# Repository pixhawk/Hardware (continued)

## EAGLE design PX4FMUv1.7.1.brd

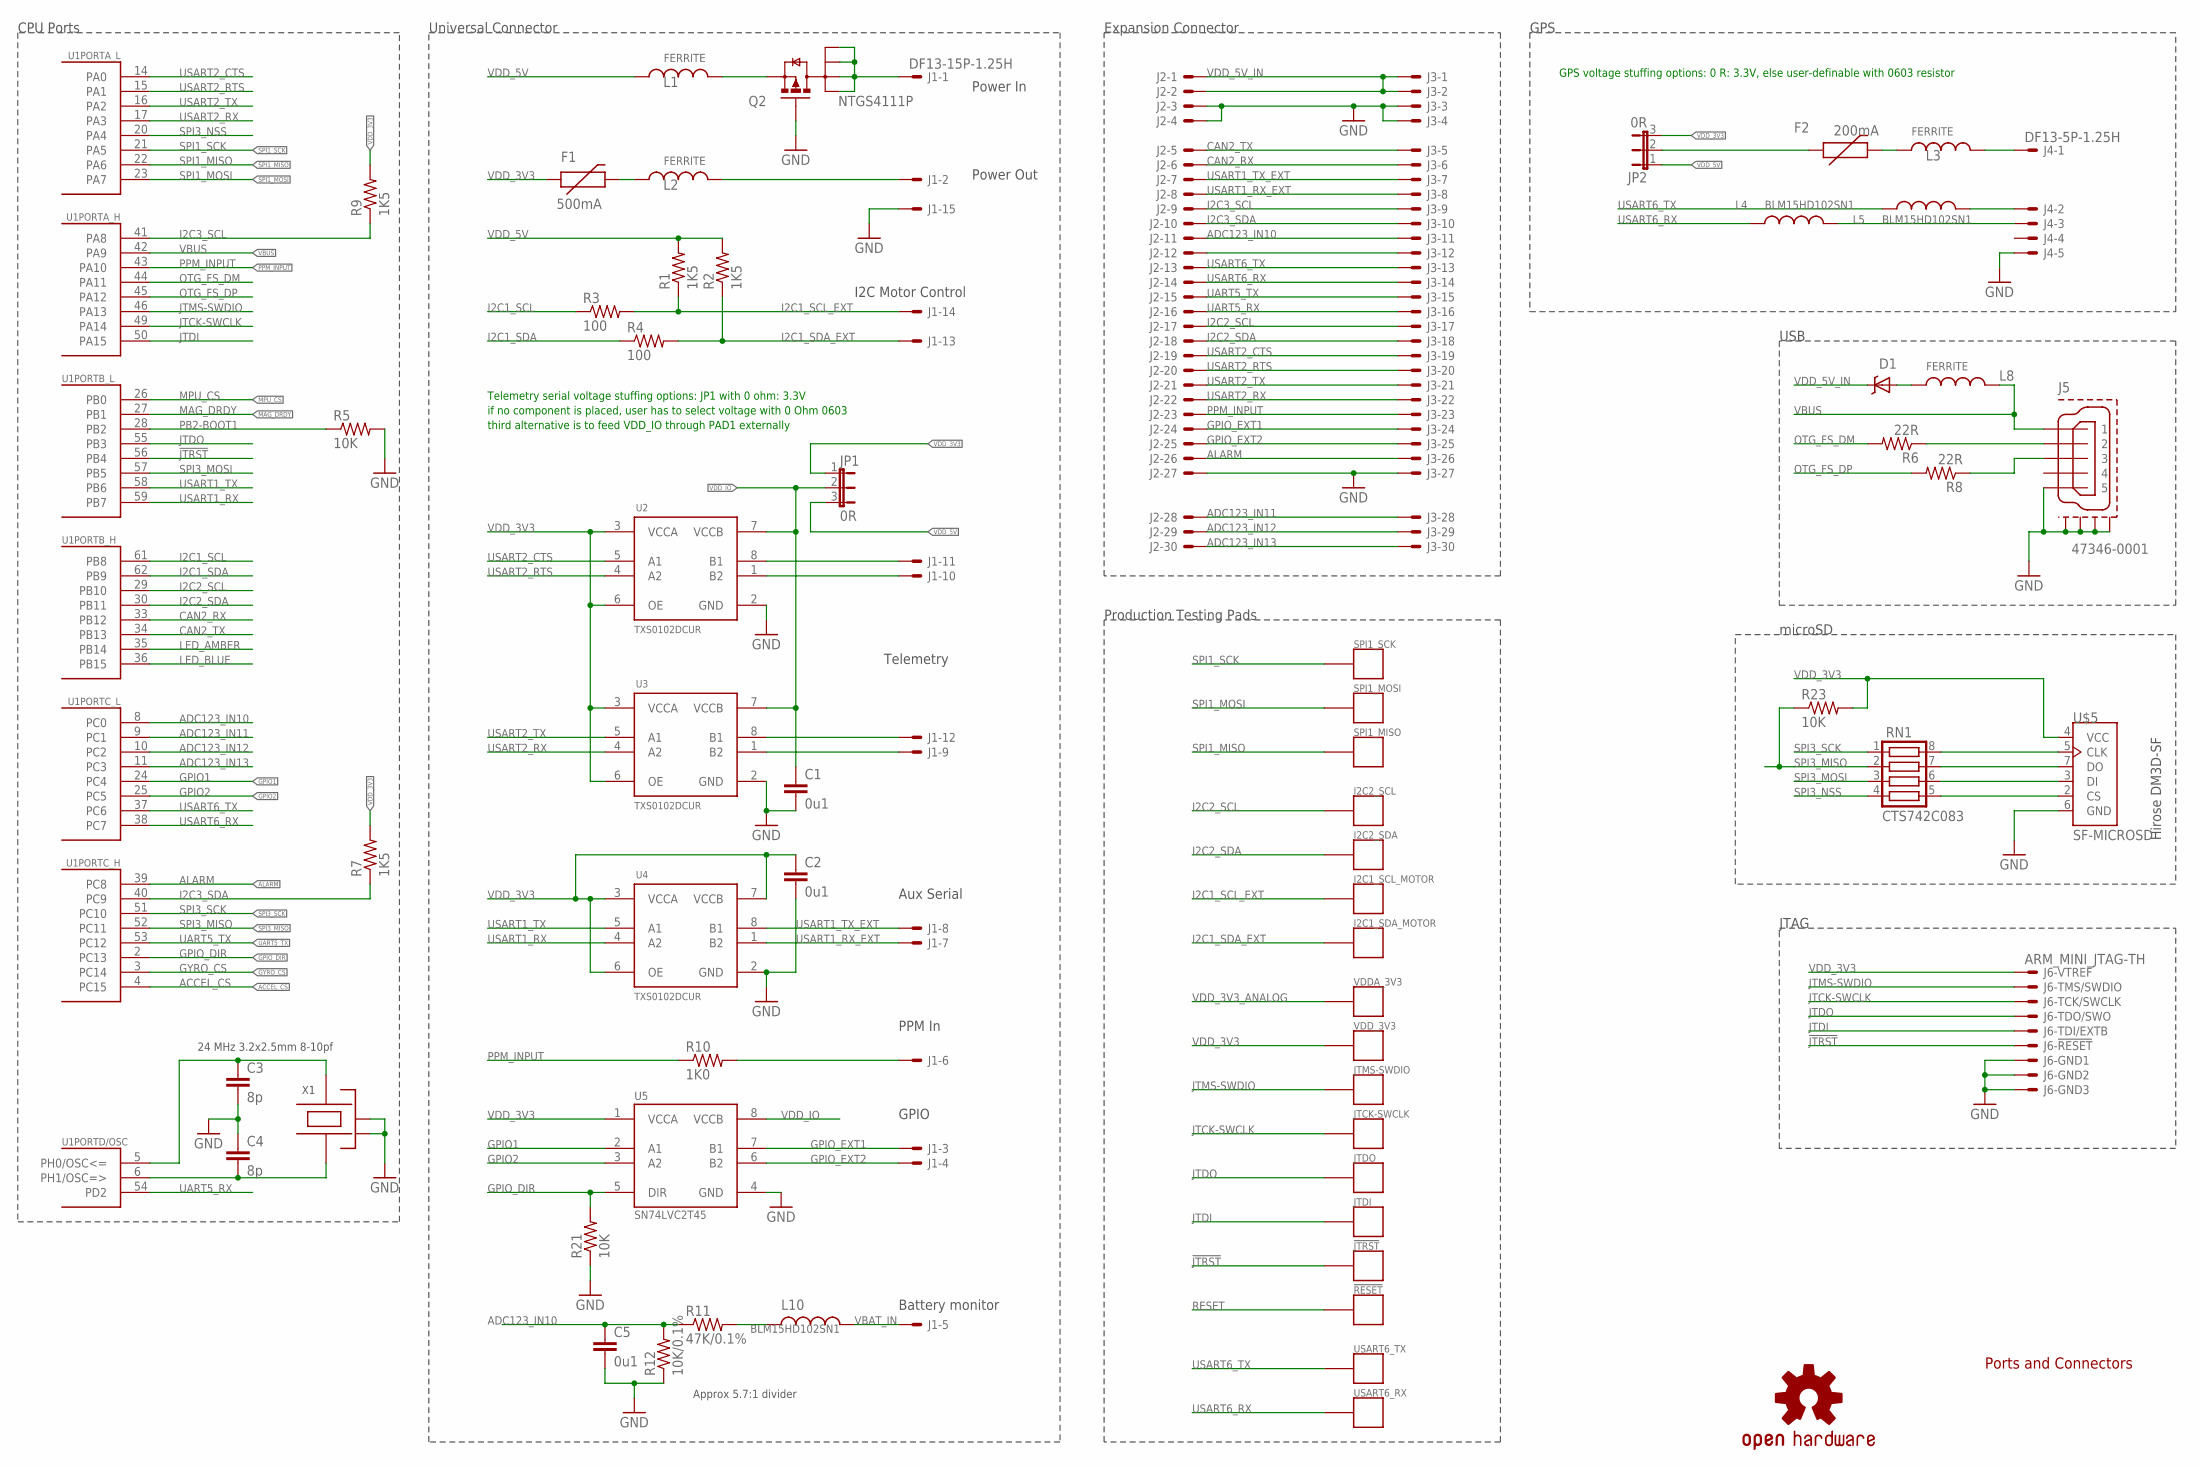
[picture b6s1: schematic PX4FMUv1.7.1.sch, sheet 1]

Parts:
!JTRST: PAD.04; PAD.04X.04; PARTNO *
!RESET: PAD.04; PAD.04X.04; PARTNO *
C1, C2, C5: 0u1; 0402-CAP; PARTNO CC0402ZRY5V7BB104
C3, C4: 8p; 0402-CAP; PARTNO C1005C0G1H080C
D1: MSS1P4-M3; MICROSMP; PARTNO MSS1P4-M3/89A
F1: 500mA; 0402-PTC; PARTNO MF-FSMF050X-2
F2: 200mA; 0402-PTC; PARTNO MF-FSMF020X-2
I2C1_SCL_MOTOR, I2C1_SDA_MOTOR, I2C2_SCL: PAD.03; PAD.03X.03; PARTNO *
I2C2_SDA: PAD.04; PAD.04X.04; PARTNO *
J1: DF13-15P-1.25H; DF13A-15P-1.25H; PARTNO DF13A-15P-1.25H(20)
J2: HEADER_2X15-REV; HEADER_2MM_2X15_REVERSE; PARTNO 953230-2000-AR-PR
J3: HEADER_2X15; HEADER_2MM_2X15; PARTNO 953230-2000-AR-PR
J4: DF13-5P-1.25H; DF13A-5P-1.25H; PARTNO DF13A-5P-1.25H(20)
J5: 47346-0001; MOLEX-47346-0001; PARTNO 47346-0001
J6: ARM_MINI_JTAG-TH; FTSH-105-01-XXX-DV; PARTNO M50-3900542
JP1, JP2: 0R; SJ_3_0603_PASTE1&2; PARTNO RMCF0402ZT0R00
JTCK-SWCLK: PAD.04; PAD.04X.04; PARTNO *
JTDI: PAD.04; PAD.04X.04; PARTNO *
JTDO: PAD.04; PAD.04X.04; PARTNO *
JTMS-SWDIO: PAD.04; PAD.04X.04; PARTNO *
L1, L2, L3, L8: FERRITE; 0402-IND; PARTNO BKP1005HS121-T
L4, L5, L10: BLM15HD102SN1; 0402-IND; PARTNO BLM15HD102SN1
Q2: NTGS4111P; TSOP-6; PARTNO NTGS4111P
R1, R2, R7, R9: 1K5; 0402-RES; PARTNO RMCF0402JT1K50
R3, R4: 100; 0402-RES; PARTNO RMCF0402JT100R
R5, R21, R23: 10K; 0402-RES; PARTNO RMCF0402FT10K0
R6, R8: 22R; 0402-RES; PARTNO RMCF0402JT22R0
R10: 1K0; 0402-RES; PARTNO RMCF0402JT1K00
R11: 47K/0.1%; 0402-RES; PARTNO ERA-2AEB473X
R12: 10K/0.1%; 0402-RES; PARTNO ERA-2AEB103X
RN1: CTS742C083; PARTNO TC164-JR-07100RL
SPI1_MISO, SPI1_MOSI, SPI1_SCK: PAD.04; PAD.04X.04; PARTNO *
U1: STM32F405RGT6; TQFP64; PARTNO STM32F405RGT6
U2, U3, U4: TXS0102DCUR; TI-DCU; PARTNO TXS0102DCUR
U5: SN74LVC2T45; TI-DCU; PARTNO SN74LVC2T45
U$5: SF-MICROSD; MICROSD
U$7: OSHW-LOGOS; OSHW-LOGO-S; PARTNO *
USART6_RX, USART6_TX: PAD.04; PAD.04X.04; PARTNO *
VDDA_3V3: PAD.04; PAD.04X.04; PARTNO *
VDD_3V3: PAD.04; PAD.04X.04; PARTNO *
X1: 24 MHz 3.2x2.5mm 8-10pf; OSCILLATOR-3.2X2.5; PARTNO NX3225SA-24.000000MHZ

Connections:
!JTRST: !JTRST.P$1, J6.10, U1.56 (PB4)
ACCEL_CS: U1.4 (PC15)
ADC123_IN10: C5.1, J2.11, J3.11, R11.1, R12.2, U1.8 (PC0)
ADC123_IN11: J2.28, J3.28, U1.9 (PC1)
ADC123_IN12: J2.29, J3.29, U1.10 (PC2)
ADC123_IN13: J2.30, J3.30, U1.11 (PC3); also elsewhere on the board
ALARM: J2.26, J3.26, U1.39 (PC8); also elsewhere on the board
CAN2_RX: J2.6, J3.6, U1.33 (PB12)
CAN2_TX: J2.5, J3.5, U1.34 (PB13)
GND: C1.2, C2.2, C3.2, C4.1, C5.2, J1.15, J2.3, J2.4, J2.27, J3.3, J3.4, J3.27, J4.5, J5.GND (5), J5.GND1, J5.GND2, J5.GND3, J5.GND4, J6.3, J6.5, J6.9, Q2.3 (G), R5.2, R12.1, R21.1, U2.2 (GND), U3.2 (GND), U4.2 (GND), U5.4 (GND), U$5.6 (GND), X1.2 (NC_2), X1.4 (NC_4); also elsewhere on the board
GPIO1: U1.24 (PC4), U5.2 (A1)
GPIO2: U1.25 (PC5), U5.3 (A2)
GPIO_DIR: R21.2, U1.2 (PC13), U5.5 (DIR)
GPIO_EXT1: J1.3, J2.24, J3.24, U5.7 (B1)
GPIO_EXT2: J1.4, J2.25, J3.25, U5.6 (B2)
GYRO_CS: U1.3 (PC14); also elsewhere on the board
I2C1_SCL: R3.1, U1.61 (PB8)
I2C1_SCL_EXT: I2C1_SCL_MOTOR.P$1, J1.14, R1.1, R3.2
I2C1_SDA: R4.1, U1.62 (PB9)
I2C1_SDA_EXT: I2C1_SDA_MOTOR.P$1, J1.13, R2.1, R4.2
I2C2_SCL: I2C2_SCL.P$1, J2.17, J3.17, U1.29 (PB10); also elsewhere on the board
I2C2_SDA: I2C2_SDA.P$1, J2.18, J3.18, U1.30 (PB11); also elsewhere on the board
I2C3_SCL: J2.9, J3.9, R9.1, U1.41 (PA8)
I2C3_SDA: J2.10, J3.10, R7.1, U1.40 (PC9)
JTCK-SWCLK: J6.4, JTCK-SWCLK.P$1, U1.49 (PA14)
JTDI: J6.8, JTDI.P$1, U1.50 (PA15)
JTDO: J6.6, JTDO.P$1, U1.55 (PB3)
JTMS-SWDIO: J6.2, JTMS-SWDIO.P$1, U1.46 (PA13)
LED_AMBER: U1.35 (PB14); also elsewhere on the board
LED_BLUE: U1.36 (PB15); also elsewhere on the board
MAG_DRDY: U1.27 (PB1); also elsewhere on the board
MPU_CS: U1.26 (PB0); also elsewhere on the board
unnamed: C4.2, U1.6 (PH1/OSC=>), X1.1
unnamed: C3.1, U1.5 (PH0/OSC<=), X1.3
unnamed: J1.2, L2.2
unnamed: F2.2, L3.1
unnamed: J4.2, L5.2
unnamed: J4.3, L4.2
unnamed: J1.11, U2.8 (B1)
unnamed: J1.10, U2.1 (B2)
unnamed: L1.2, Q2.4 (S)
unnamed: J1.12, U3.8 (B1)
unnamed: J1.9, U3.1 (B2)
unnamed: F2.1, JP2.2
unnamed: J2.12, J3.12
unnamed: RN1.5, U$5.2 (CS)
unnamed: D1.ANODE (A), L8.1
unnamed: J4.1, L3.2
unnamed: RN1.6, U$5.3 (DI)
unnamed: F1.2, L2.1
unnamed: RN1.7, U$5.7 (DO)
unnamed: RN1.8, U$5.5 (CLK)
unnamed: L10.1, R11.2
unnamed: J1.1, Q2.1 (D), Q2.2 (D1), Q2.5 (D2), Q2.6 (D3)
OTG_DM: J5.D- (2), R6.1
OTG_DP: J5.D+ (3), R8.1
OTG_FS_DM: R6.2, U1.44 (PA11)
OTG_FS_DP: R8.2, U1.45 (PA12)
PB2-BOOT1: R5.1, U1.28 (PB2)
PPM_INPUT: J2.23, J3.23, R10.1, U1.43 (PA10)
PPM_INPUT_CON: J1.6, R10.2
RESET: !RESET.P$1; also elsewhere on the board
SPI1_MISO: SPI1_MISO.P$1, U1.22 (PA6); also elsewhere on the board
SPI1_MOSI: SPI1_MOSI.P$1, U1.23 (PA7); also elsewhere on the board
SPI1_SCK: SPI1_SCK.P$1, U1.21 (PA5); also elsewhere on the board
SPI3_MISO: R23.1, RN1.2, U1.52 (PC11)
SPI3_MOSI: RN1.3, U1.57 (PB5)
SPI3_NSS: RN1.4, U1.20 (PA4)
SPI3_SCK: RN1.1, U1.51 (PC10)
UART5_RX: J2.16, J3.16, U1.54 (PD2)
UART5_TX: J2.15, J3.15, U1.53 (PC12)
USART1_RX: U1.59 (PB7), U4.4 (A2)
USART1_RX_EXT: J1.7, J2.8, J3.8, U4.1 (B2)
USART1_TX: U1.58 (PB6), U4.5 (A1)
USART1_TX_EXT: J1.8, J2.7, J3.7, U4.8 (B1)
USART2_CTS: J2.19, J3.19, U1.14 (PA0), U2.5 (A1)
USART2_RTS: J2.20, J3.20, U1.15 (PA1), U2.4 (A2)
USART2_RX: J2.22, J3.22, U1.17 (PA3), U3.4 (A2)
USART2_TX: J2.21, J3.21, U1.16 (PA2), U3.5 (A1)
USART6_RX: J2.14, J3.14, L4.1, U1.38 (PC7), USART6_RX.P$1
USART6_TX: J2.13, J3.13, L5.1, U1.37 (PC6), USART6_TX.P$1
VBAT_IN: J1.5, L10.2; also elsewhere on the board
VBUS: J5.VBUS (1), L8.2, U1.42 (PA9)
VDD_3V3: C2.1, F1.1, J6.1, JP1.1, JP2.3, R7.2, R9.2, R23.2, U2.3 (VCCA), U2.6 (OE), U3.3 (VCCA), U3.6 (OE), U4.3 (VCCA), U4.6 (OE), U4.7 (VCCB), U5.1 (VCCA), U$5.4 (VCC), VDD_3V3.P$1; also elsewhere on the board
VDD_3V3_ANALOG: VDDA_3V3.P$1; also elsewhere on the board
VDD_5V: JP1.3, JP2.1, L1.1, R1.2, R2.2; also elsewhere on the board
VDD_5V_IN: D1.CATHODE (C), J2.1, J2.2, J3.1, J3.2; also elsewhere on the board
VDD_IO: C1.1, JP1.2, U2.7 (VCCB), U3.7 (VCCB), U5.8 (VCCB)

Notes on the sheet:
Ports and Connectors
Telemetry
I2C Motor Control
Power In
Battery monitor
GPIO
Approx 5.7:1 divider
CPU Ports
Universal Connector
GPS
USB
JTAG
GPS voltage stuffing options: 0 R: 3.3V, else user-definable with 0603 resistor
Telemetry serial voltage stuffing options: JP1 with 0 ohm: 3.3V
Aux Serial
PPM In
Expansion Connector
if no component is placed, user has to select voltage with 0 Ohm 0603
Production Testing Pads
Power Out
microSD
third alternative is to feed VDD_IO through PAD1 externally
Hirose DM3D-SF

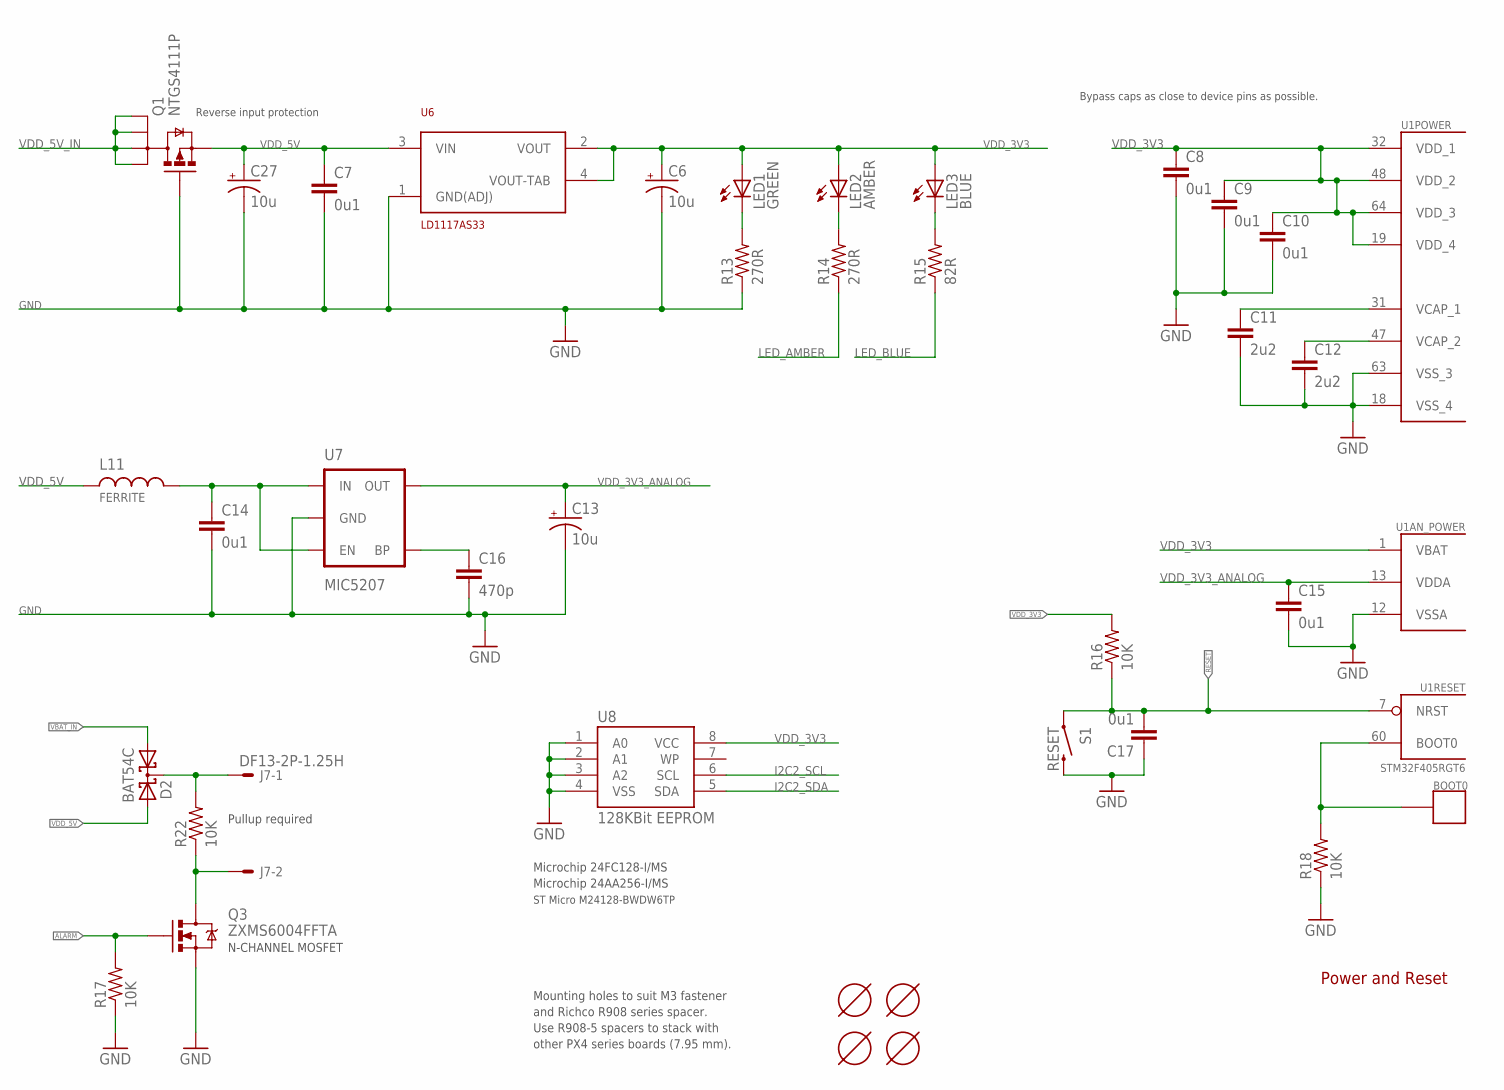
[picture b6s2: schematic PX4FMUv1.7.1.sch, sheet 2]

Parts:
BOOT0: PAD.04; PAD.04X.04; PARTNO *
C6, C13, C27: 10u; EIA3216; PARTNO F931A106MAA
C7, C8, C9, C10, C14, C15, C17: 0u1; 0402-CAP; PARTNO CC0402ZRY5V7BB104
C11, C12: 2u2; 0402-CAP; PARTNO C1608Y5V1C225Z
C16: 470p; 0402-CAP; PARTNO CC0402KRX7R9BB471
D2: BAT54C; SOT23-3; PARTNO BAT54C-7-F
J7: DF13-2P-1.25H; DF13A-2P-1.25H; PARTNO DF13-2P-1.25H(20)
L11: FERRITE; 0402-IND; PARTNO BKP1005HS121-T
LED1: GREEN; LED-0603; PARTNO LNJ337W83RA
LED2: AMBER; LED-0603; PARTNO LNJ437W84RA
LED3: BLUE; LED-0603; PARTNO LNJ937W8CRA
Q1: NTGS4111P; TSOP-6; PARTNO NTGS4111P
Q3: ZXMS6004FFTA; SOT23-3; PARTNO ZXMS6004FFTA
R13, R14: 270R; 0402-RES; PARTNO RC0402JR-07270RL
R15: 82R; 0402-RES; PARTNO RC0402JR-0782RL
R16, R17, R18, R22: 10K; 0402-RES; PARTNO RMCF0402FT10K0
S1: RESET; EVQP7J01K; PARTNO EVQP7J01K
U1: STM32F405RGT6; TQFP64; PARTNO STM32F405RGT6
U6: LD1117AS33; SOT-223; PARTNO LD1117AS33
U7: MIC5207; SOT23-5; PARTNO MIC5207-3.3YM5
U8: 128KBit EEPROM; MSOP-8; PARTNO 24FC128-I/MS
U$1, U$2, U$3, U$4: MOUNT-HOLE3.1MM; MOUNT-HOLE3.1; PARTNO *

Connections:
ALARM: Q3.1 (G), R17.2; also elsewhere on the board
BOOT0: BOOT0.P$1, R18.2, U1.60 (BOOT0)
GND: C6.C (-), C7.2, C8.2, C9.2, C10.2, C11.2, C12.2, C13.C (-), C14.2, C15.2, C16.2, C17.1, C27.C (-), Q1.3 (G), Q3.2 (S), R13.1, R17.1, R18.1, S1.B3 (2), U1.12 (VSSA), U1.18 (VSS_4), U1.63 (VSS_3), U6.1 (GND(ADJ)), U7.2 (GND), U8.1 (A0), U8.2 (A1), U8.3 (A2), U8.4 (VSS); also elsewhere on the board
I2C2_SCL: U8.6 (SCL); also elsewhere on the board
I2C2_SDA: U8.5 (SDA); also elsewhere on the board
LED_AMBER: R14.1; also elsewhere on the board
LED_BLUE: R15.1; also elsewhere on the board
unnamed: D2.3 (CC), J7.1, R22.2
unnamed: C16.1, U7.4 (BP)
unnamed: J7.2, Q3.3 (D), R22.1
unnamed: LED3.C, R15.2
unnamed: LED1.C, R13.2
unnamed: LED2.C, R14.2
unnamed: C14.1, L11.2, U7.1 (IN), U7.3 (EN)
RESET: C17.2, R16.1, S1.A1 (1), U1.7 (NRST); also elsewhere on the board
VBAT_IN: D2.1 (A1); also elsewhere on the board
VCAP_1: C11.1, U1.31 (VCAP_1)
VCAP_2: C12.1, U1.47 (VCAP_2)
VDD_3V3: C6.A (+), C8.1, C9.1, C10.1, LED1.A, LED2.A, LED3.A, R16.2, U1.1 (VBAT), U1.19 (VDD_4), U1.32 (VDD_1), U1.48 (VDD_2), U1.64 (VDD_3), U6.2 (VOUT), U6.4 (VOUT-TAB), U8.8 (VCC); also elsewhere on the board
VDD_3V3_ANALOG: C13.A (+), C15.1, U1.13 (VDDA), U7.5 (OUT); also elsewhere on the board
VDD_5V: C7.1, C27.A (+), D2.2 (A2), L11.1, Q1.4 (S), U6.3 (VIN); also elsewhere on the board
VDD_5V_IN: Q1.1 (D), Q1.2 (D1), Q1.5 (D2), Q1.6 (D3); also elsewhere on the board

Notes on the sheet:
Power and Reset
Bypass caps as close to device pins as possible.
Microchip 24FC128-I/MS
Microchip 24AA256-I/MS
Mounting holes to suit M3 fastener
and Richco R908 series spacer.
ST Micro M24128-BWDW6TP
Reverse input protection
N-CHANNEL MOSFET
Pullup required
Use R908-5 spacers to stack with
other PX4 series boards (7.95 mm).

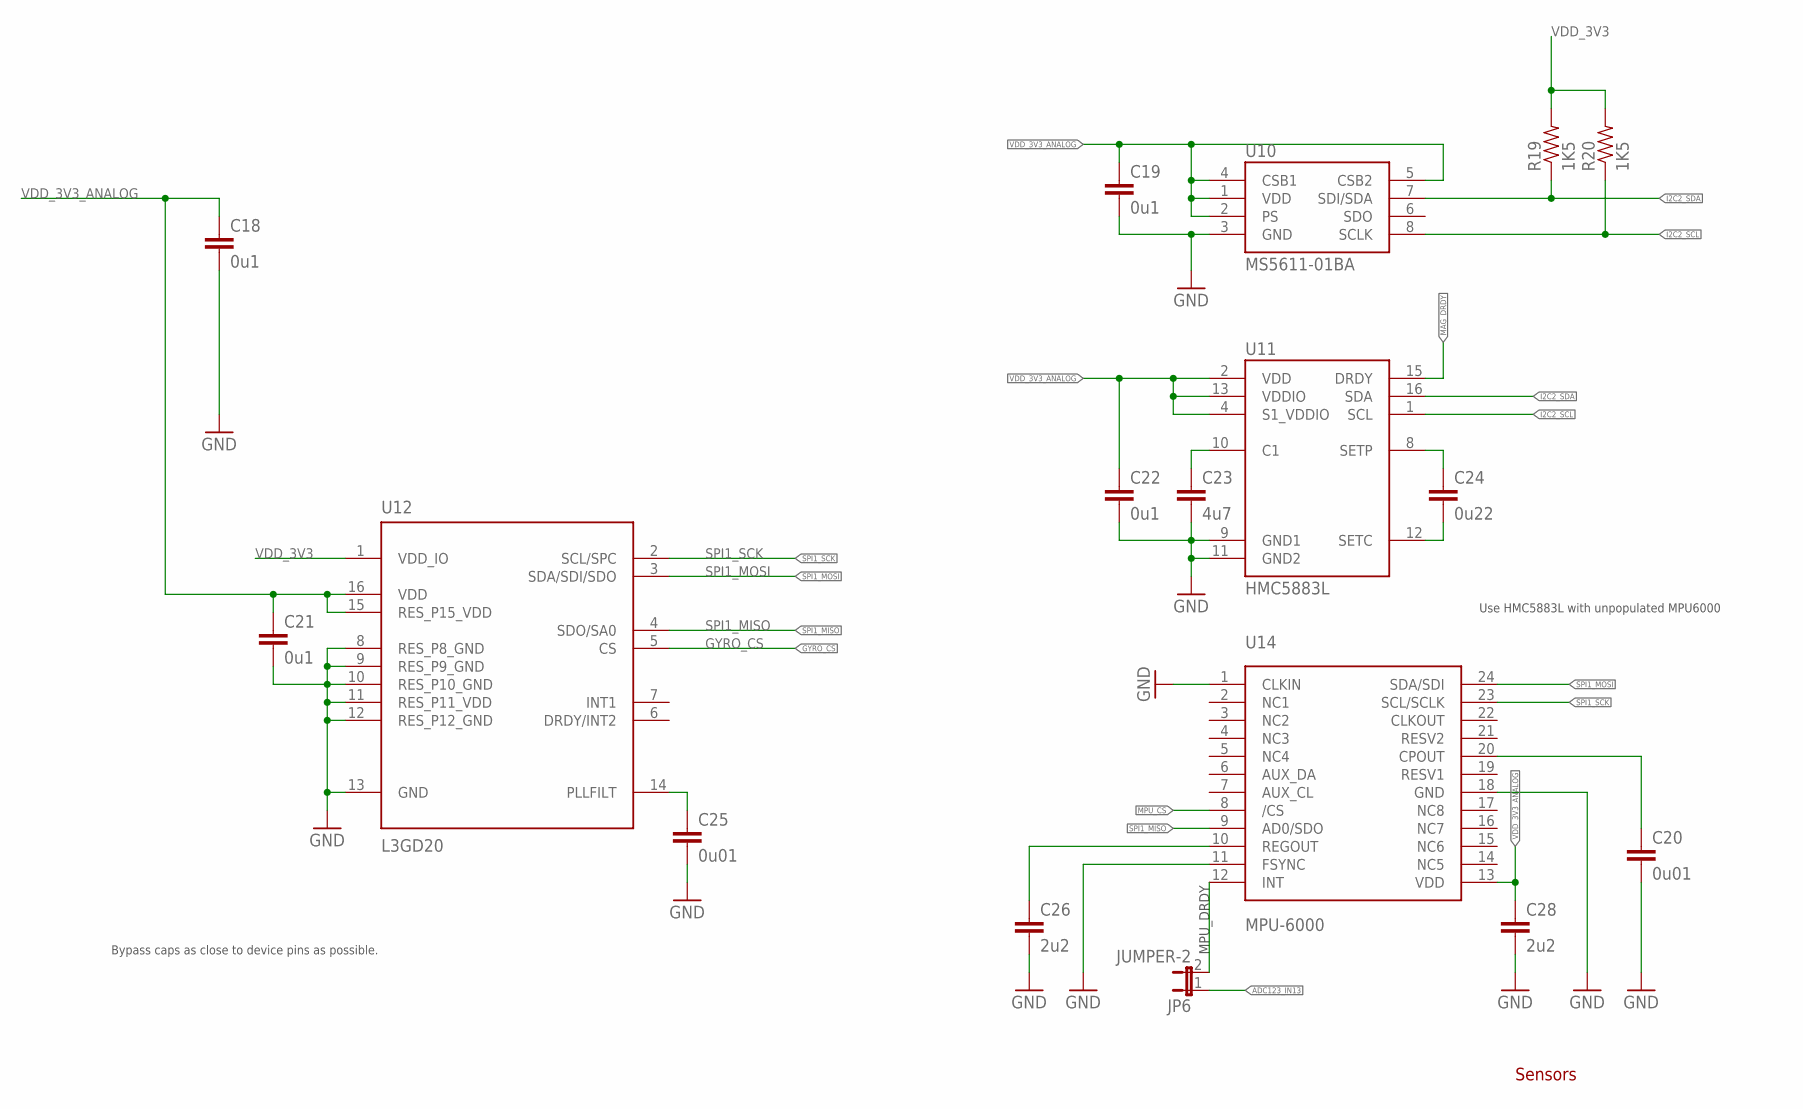
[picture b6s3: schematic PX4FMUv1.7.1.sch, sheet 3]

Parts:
C18, C19, C21, C22: 0u1; 0402-CAP; PARTNO CC0402ZRY5V7BB104
C20, C25: 0u01; 0402-CAP; PARTNO CC0402KRX7R7BB103
C23: 4u7; 0402-CAP; PARTNO C1608Y5V0J475Z
C24: 0u22; 0402-CAP; PARTNO C1005Y5V1C224Z
C26, C28: 2u2; 0402-CAP; PARTNO C1608Y5V1C225Z
JP6: JUMPER-2; SJ_2
R19, R20: 1K5; 0402-RES; PARTNO RMCF0402JT1K50
U10: MS5611-01BA; PARTNO MS5611-01BA
U11: HMC5883L; HMC5883L-MAN; PARTNO HMC5883L
U12: L3GD20; L3G4200DH-MAN; PARTNO L3GD20
U14: MPU-6000; QFN-24; PARTNO MPU-6000

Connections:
ADC123_IN13: JP6.1; also elsewhere on the board
GND: C18.2, C19.2, C20.2, C21.2, C22.2, C23.2, C25.2, C26.2, C28.2, U10.3 (GND), U11.9 (GND1), U11.11 (GND2), U12.8 (RES_P8_GND), U12.9 (RES_P9_GND), U12.10 (RES_P10_GND), U12.11 (RES_P11_VDD), U12.12 (RES_P12_GND), U12.13 (GND), U14.1 (CLKIN), U14.11 (FSYNC), U14.18 (GND); also elsewhere on the board
GYRO_CS: U12.5 (CS); also elsewhere on the board
I2C2_SCL: R20.1, U10.8 (SCLK), U11.1 (SCL); also elsewhere on the board
I2C2_SDA: R19.1, U10.7 (SDI/SDA), U11.16 (SDA); also elsewhere on the board
MAG_DRDY: U11.15 (DRDY); also elsewhere on the board
MPU_CS: U14.8 (/CS); also elsewhere on the board
unnamed: C24.1, U11.8 (SETP)
unnamed: C24.2, U11.12 (SETC)
unnamed: C25.1, U12.14 (PLLFILT)
unnamed: C23.1, U11.10 (C1)
unnamed: C20.1, U14.20 (CPOUT)
unnamed: C26.1, U14.10 (REGOUT)
unnamed: JP6.2, U14.12 (INT)
SPI1_MISO: U12.4 (SDO/SA0), U14.9 (AD0/SDO); also elsewhere on the board
SPI1_MOSI: U12.3 (SDA/SDI/SDO), U14.24 (SDA/SDI); also elsewhere on the board
SPI1_SCK: U12.2 (SCL/SPC), U14.23 (SCL/SCLK); also elsewhere on the board
VDD_3V3: R19.2, R20.2, U12.1 (VDD_IO); also elsewhere on the board
VDD_3V3_ANALOG: C18.1, C19.1, C21.1, C22.1, C28.1, U10.1 (VDD), U10.2 (PS), U10.4 (CSB1), U10.5 (CSB2), U11.2 (VDD), U11.4 (S1_VDDIO), U11.13 (VDDIO), U12.15 (RES_P15_VDD), U12.16 (VDD), U14.13 (VDD); also elsewhere on the board

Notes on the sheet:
Sensors
Bypass caps as close to device pins as possible.
Use HMC5883L with unpopulated MPU6000
MPU_DRDY

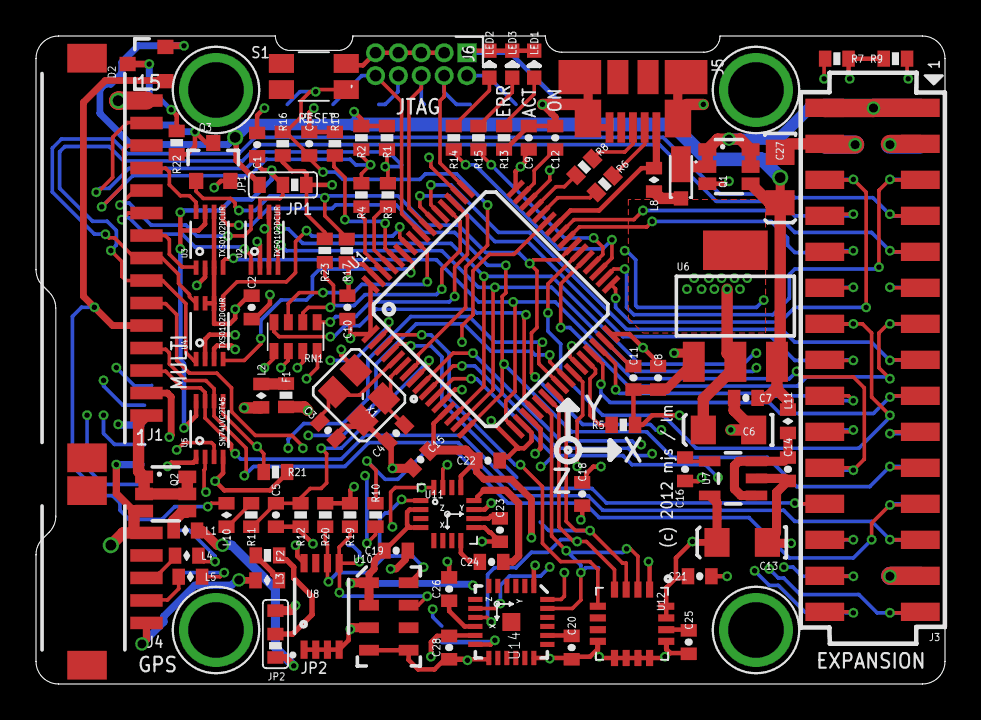
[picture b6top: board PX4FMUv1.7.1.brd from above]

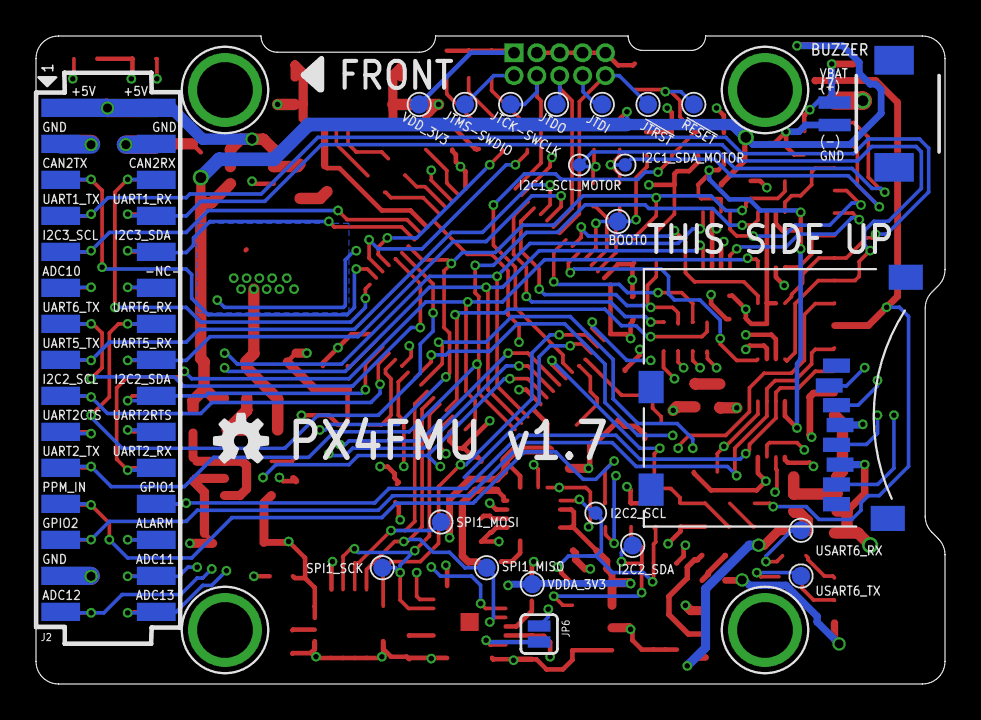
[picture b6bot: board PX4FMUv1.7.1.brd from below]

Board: 4 copper layers, 50.5 x 36.0 mm, 118 parts (23 on the bottom side), 104 nets.

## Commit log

2012-09-08 Initial import
2013-01-30 Release files for PX4FMU v1.7.1
2013-10-09 FMU v2.3 release, as the HW is now shipping to customers of Iris
2013-10-25 Updates to reflect questions asked on mailing list https://groups.google.com/forum/#!topicsearchin/px4users/mosfet%7Csort:date/px4users/fcfwdMKPhbI
2014-01-02 Checking in FMU v2.4, as it ships now
2014-01-02 Added final sub-rev now shipping
2014-01-04 Added disclaimer
2014-01-06 Airspeed sensing
2014-01-06 Missing file
2014-03-04 Added flow sensor
2014-05-27 FMU v2.4.5 published - changes values of C1108 / C1109 / C1110 to 10p/25V. NO SCHEMATIC OR BOARD CHANGES.
2014-07-29 Check in WIP 2.4.6 design. Robustified against misbehaving RC receivers (excessive current, reverse overvoltage)
2014-11-26 FMU v2.4.5 sch mistake fix - C1110 to 10p
2014-11-28 Update README.md
    Edited bobstarr url because old url retrieve an 404 error
2014-11-28 Resolved all formatting to allow table view to work
    All comma's within data are currently included via the html code &#44;
    if you wish to revert them locally.
2014-11-28 examples of csv data
    testing copies to show issue with commas
2014-11-29 Replacing commas
    Issue with github identified and worked around, commas are back with
    line 17 being the only exception, one comma had to come out while they
    resolve the issues, but helped them identify several cases of weird
    behavior.
2014-11-29 Revert "Update commadelimited with doublequotes.csv"
    This reverts commit 0b8803a83093e91ba2a47e4f7a5aab0cbd2a912b.
2014-11-29 Revert "examples of csv data"
    This reverts commit a9a1a6167c3542b1fdea61d455a3e74296f0ccc0.
2014-12-13 Ignore temporary files
2014-12-13 Add PDF rendering of FMUv2.4.5
2015-06-06 Import Pixhawk 2 / FMUv3 design files
2015-11-24 Move PX4 IOv1 boards to their own folder
2015-11-24 Move FMUv1 to its own folder
2015-11-24 Move FLOW to its own folder
2015-11-24 Move airspeed to its own folder
2015-11-24 Remove unfinished 2.4.6 rev
2015-11-24 Move FMUv2 boards to their own folder
2015-11-26 Add Gitter badge
2015-11-27 px4fmu 2.4.6 initial commit: Q601 and R620 deleted, R621=220R from VDD_3V3_SENSORS to GND
2016-05-06 Add MindPXv2 hardware
2016-10-20 Sapog HW - initial commit
2016-10-31 Add new MindPX v2.8 and MindRacer V1.2 hardware
2016-11-08 correct verbage issues
2016-11-15 Updated description of the Sapog ESC hardware
2016-11-21 Add documents link of MindRacer
2017-07-18 Updated the Sapog links
2018-04-03 Fixed the BOM entry of the power decoupling capacitor. 25 V tantalum capacitors degrade quickly, the new recommendation is to use 35 V rated capacitors. For more info, see https://forum.zubax.com/t/c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
2018-04-03 Added design guidelines to README; also removed the note that the design is not recommended for manufaturing, since it has been manufactured at least once and confirmed to work properly
2018-04-03 Added another item to the design guidelines
2018-04-13 added a link to FMUv4-Pixracer git repo
2018-05-06 added datasheet and pinout
2018-05-08 added pixhawk 4 pinouts
2018-05-14 modified power pinout and renamed datasheet
2018-06-27 Add updated data sheet-to PX4v1.8
2019-05-24 Clarify FMU Open Design Usage
2019-05-24 Update entry point
2019-05-24 Minimum changes to make FMU-centric
2019-05-30 Better structure definitions
2019-05-30 Fix table
2019-05-30 Add placeholder for public developer call
2019-06-07 Tidy up definitions. Split out license and trademarks
2019-06-07 Add dev call info
2019-06-07 Improve table describing FMU differences
2019-06-07 Remove the 5MX link
2019-06-07 Add FMUv5 readme
2019-06-07 Add more useful text for FMUv1, FMUv3
2019-06-07 Update all files, removing placholders.
2019-06-07 Better highlight links to parent docs
2019-06-07 Move FMUv4
2019-06-07 Improve visibility of link to home
2019-06-11 Readme - fix devcall link
2019-11-22 README: fix FMUv5 swapped columns
    The Lead Product and CPU columns were swapped for the FMUv5 in the FMU version table
2020-04-13 Adding 2020 April version Pixhawk Autopilot Reference Standard
2020-04-13 Create FMUv5X folder
2020-04-13 adding ref standard PDF
2020-04-13 Adding FMUv6X folder
2020-04-13 adding pixhawk trademark guidelines v1
2020-04-14 Revert "Adding FMUv6X folder"
    This reverts commit d537555fe447c5ef65214fc301e8cf7781a98bb9.
2020-04-14 Revert "Create FMUv5X folder"
    This reverts commit 0809c3b45ebc501ff589e9a858da88f1dbf9627f.
2020-04-14 Revert "adding ref standard PDF"
    This reverts commit 4f5af0da7ce8a70f4e25d96556b8f1692d800be0.
2020-04-14 Revert "adding ref standard PDF"
    This reverts commit 32735e045ad6930dfd2c3175fce6cc0cf453981a.
2020-04-14 Revert "Adding 2020 April version Pixhawk Autopilot Reference Standard"
    This reverts commit 7c0f774a1ad7a32e6d8a0e0252287958cc2a9872.
2020-04-14 Revert "adding pixhawk trademark guidelines v1"
    This reverts commit 09315c606763ed95200e19dbccc4955948344ee6.
2020-05-21 Correct CPU frequency in README.md
2022-05-12 add altium source file for PRI breakout board
2022-05-12 add readme for PRI
2022-05-13 add lincese to PRI files
2022-05-16 Release Pixhawk Debug Adapter
2022-05-18 Release Pixhawk Debug Adapter (#110)
2022-08-25 Galeri
    Photo video
